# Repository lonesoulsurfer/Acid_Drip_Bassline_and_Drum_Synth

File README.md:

# Acid Drip - Bassline Synth, Drift Synth & Drum Machine

Youtube Video (click the image) -  

An RP2040-based acid bassline synthesizer and drum machine built on the Mozzi audio library. Three instruments in one device: a 16-step acid sequencer, a second synth voice called DRIFT, and a 16-pattern drum groove box, all running simultaneously on dual cores with a 320x240 ILI9341 TFT display and 16 Cherry MX pads.

NOTE: the images of the synth are V1. V2 is what I have provided in this repo and looks a little different (extra pot for mix added).

NOTE: V5 firmware adds a second synth voice called DRIFT, pattern chaining for the acid save slots, a MIX EDIT mode for balancing all three engines against each other, and a user editable custom drum pattern, on top of everything V4 had. See DRIFT Synth, Pattern Chaining, MIX EDIT and Custom Pattern below for each.

<p align="center">
  
  &nbsp;
  
  &nbsp;
  
</p>

---

## Hardware

| Component | Detail |
|-----------|--------|
| MCU | RP2040 (Raspberry Pi Pico or equivalent) |
| Display | ILI9341 320x240 TFT |
| Pads | 16x Cherry MX switches (2 rows of 8) |
| Pots | 3x analog (CUT, RES, DECAY) |
| Audio out (acid) | GP15 -> 100R + 10nF RC filter -> 3.5mm jack |
| Audio out (drums) | GP2 -> 470R resistor -> 3.5mm jack. In V5 this output also carries the DRIFT synth voice, summed with the drums |
| Sync in/out | GP2 (hardware SPDT switch selects drum/DRIFT audio OR sync). Direction (in or out) is chosen from an on-screen menu at boot, see Sync In/Out below |

### Wiring

```
TFT   : SCK=GP6  SDA=GP7  RST=GP8  DC=GP10  CS=GP13
Pots  : CUT=GP26  RES=GP28  DCY=GP27
Sync  : IN/OUT=GP2
Audio : Acid=GP15   Drums/DRIFT=GP2

Top row pads (steps 1-8):
  GP14=pad1  GP12=pad2  GP11=pad3  GP16=pad4
  GP17=pad5  GP19=pad6  GP20=pad7  GP21=pad8

Bottom row pads (steps 9-16 / FUNC select):
  GP0=pad9   GP1=pad10  GP3=pad11  GP4=pad12
  GP5=pad13  GP9=pad14  GP18=pad15 GP22=pad16
```

---

## Dependencies

Install via Arduino Library Manager:

- **Mozzi** (audio synthesis engine)
- **Adafruit GFX**
- **Adafruit ILI9341**

Board package: **Raspberry Pi Pico/RP2040** (Earle Philhower core)

---

## Files

This repo has two firmware versions, each in its own folder. They are separate sketches, not meant to be merged.

### V4 (`Acid_Drip_Drum_Acid_V4`)

| File | Description |
|------|-------------|
| `Acid_Drip_V4.ino` | Main sketch, acid synth engine, sequencer, UI |
| `BeatMachine_V4.ino` | Drum machine tab, DrumKid engine, 8 instruments |
| `beats.h` | 16 preset drum patterns (techno, house, hip-hop, etc.) |
| `sample0-7.h` | Drum samples stored as int8 arrays in flash (PROGMEM) |

### V5 (`Acid_Drip_Drum_Acid_Drift_V5`)

| File | Description |
|------|-------------|
| `Acid_Drip_V5_Drum_Acid_Drift.ino` | Main sketch, acid synth engine, sequencer, UI, MIX EDIT |
| `Drift.ino` | DRIFT tab, the second synth voice engine |
| `BeatMachine2.ino` | Drum machine tab, DrumKid engine, 8 instruments, custom pattern editor |
| `beats.h` | 16 drum patterns: 15 fixed presets plus one user editable CUSTOM slot |
| `sample0-7.h` | Drum samples stored as int8 arrays in flash (PROGMEM) |

V5 adds a second synth voice (DRIFT), pattern chaining, per engine level mixing (MIX EDIT), and a user editable custom drum pattern, all on top of everything V4 already had. Pick whichever folder matches the firmware you want to flash.

---

## Acid Synthesizer

### Pad Layout

```
+---------+---------+---------+---------+---------+---------+---------+---------+
|    1    |    2    |    3    |    4    |    5    |    6    |    7    |    8    |
|  step   |  step   |  step   |  step   |  step   |  step   |  step   |  step   |
|    1    |    2    |    3    |    4    |    5    |    6    |    7    |    8    |
+---------+---------+---------+---------+---------+---------+---------+---------+
|    9    |   10    |   11    |   12    |   13    |   14    |   15    |   16    |
|   KEY   |  RIFF   |  SOUND  |  WALK   |   FX    |  TEMPO  |  PLEN   |  PAT>   |
+---------+---------+---------+---------+---------+---------+---------+---------+
  (bottom row labels show only in FUNC mode)
```

### Step Editing

| Action | Result |
|--------|--------|
| Short press a pad | Toggle step on/off |
| Long press x1 | Toggle accent |
| Long press x2 | Toggle glide |
| Hold pad + turn CUT pot | Set step note (scale-quantised) |

### Chords

| Chord | Action |
|-------|--------|
| Pads 1+2 | Play / Stop |
| Pads 1+2 (hold 0.5s) | Factory reset. V5 scopes this to whichever engine is currently the edit focus: acid or DRIFT. Drums have their own separate reset, hold pads 1+2 for 1s while in drum mode |
| Pads 7+8 | Enter / exit FUNC mode |
| Pads 9+10 | Switch to drums (from acid or DRIFT), or back to whichever of acid/DRIFT was last active (from drums) |
| Pads 9+10+11 (hold 0.5s) | V5 only. From acid: go to DRIFT. From DRIFT: back to acid. From drums: no-op, see DRIFT Synth below |
| Pads 11+12+13+14 (hold 1s) | Toggle Acid Walks easter egg |
| Pads 12+13 | Enter / exit chain-build mode |
| Pads 15+16 (hold 1s) | V5 only. Toggle MIX EDIT mode (replaces V4's Accent Edit, see below) |

### Save / Load (hold pads 7+8)

- **Tap** pads 3/4/5/6 to load from slot 1/2/3/4
- **Hold** pads 3/4/5/6 for 1 second to save to slot 1/2/3/4
- Slot status shown top-right (yellow dot = saved, grey = empty)

In V5, each slot saves and loads the acid pattern, DRIFT, and the drum beat together, whichever of the three actually have data saved in that slot. The gesture is identical from the acid screen or the drum screen; either one saves and loads all three engines at once. Loading a slot also restores each engine's play/stop state exactly as it was at save time: an engine that was stopped when you saved goes silent on load even if it is currently playing, and an engine that was playing starts up again, in sync with the others. Any engine with no data in that slot is left exactly as it currently is. Tapping an empty slot shows an "empty" indicator instead of loading anything. In V4, a slot only covered whichever single engine you were on when you saved, and play state was not part of it.

Holding pads 3+4+5+6 together for 1 second, while on the acid or DRIFT screen, wipes the acid pattern out of all 4 slots at once (a "clear all" separate from the per-slot save/hold gesture above). Because V5 slots hold all three engines together, this only clears the acid portion of each slot; any DRIFT or drum data saved in those same slot numbers is left alone. This gesture is unchanged from V4, it was already in the firmware but missing from this document.

### Pattern Chaining (V5 only)

Link the 4 save slots into a longer playback sequence, up to 16 positions, in any order, with repeats.

**Building a chain:**

1. Tap pads 12+13 together to enter chain-build mode. The screen switches to a dedicated chain-builder view.
2. Tap pads 3/4/5/6 to append that slot to the chain. Tapping the same pad more than once repeats that slot, for example tapping 3, 3, 4, 5, 6, 6 builds a chain that plays slot 1 twice, then slot 2, slot 3, and slot 4 twice.
3. Tap pads 12+13 again to exit and start playback. The chain begins automatically, even if nothing was playing yet.

Each chain position plays through one full loop of that slot's own saved pattern length before advancing to the next position: a slot saved at 16 steps plays 16 steps, a slot saved at 8 steps plays 8, and so on. When the chain reaches the end it loops back to the first position.

Pads 7+8 (FUNC) cancel an in-progress build without starting playback. Tapping 12+13 again at any other time, including while a chain is already playing, drops the current chain and starts a fresh build.

A small "CH" indicator appears next to the slot status dots whenever a chain is actively playing.

Chains are session-only and are not saved to EEPROM, so rebuilding one takes a few seconds if needed again after a power cycle. Chaining currently works in the acid synth only, not drum mode.

### FUNC Mode (enter with pads 7+8)

| Pad | Function | Options |
|-----|----------|---------|
| 9 | KEY | Root note: C D Eb F G Ab Bb B |
| 10 | RIFF | Load preset riff pattern: DFLT / SQNCE / FUNK / MINI / JUMP / RAVE / SYNC / DARK |
| 11 | SOUND | Synth voice: SAW / SQR / SINE / PWM / CSAW / CSQR / CSIN / SUBSQ |
| 12 | WALK | Note walk: OFF / 4TH / OCTWAVE / 5TH / BOUNCE / MIN3RD / VAMP3 / RANDOM |
| 13 | FX | Enter FX assign sub-mode |
| 14 | TEMPO | Preset BPM: 100/110/120/128/133/138/145/160, or tap repeatedly for tap tempo |
| 15 | PLEN | Pattern length: 1 / 2 / 3 / 4 / 6 / 8 / 12 / 16 |
| 16 | PAT> | Playback order: FWD / CW / ALT / REV / SKIP2 / SKIP3 / PING / RND |

> Note: there is currently no live scale-type or octave selector. `seq.scale`/`seq.octave` are only set when loading a saved patch slot.

### FX Assign (FUNC -> pad 13)

1. Press a top-row pad to select an effect:
   `None / Oct Up / Retrigger / Stutter / Maj Step / Min Step / Dom7 Step / Dim Step`
2. Press any pad 1-16 to assign that effect to that step.
3. Tap the selected FX pad again to deselect.
4. Long-hold pad 1 to clear all step effects.
5. Pads 7+8 to exit back to main screen.

### MIX EDIT (V5 only)

Hold **pads 15+16** for 1 second to enter MIX EDIT. The three pots trim the output level of each of the three engines independently:

| Pot | Engine |
|-----|--------|
| CUT | Acid |
| RES | DRIFT |
| DCY | Drums |

This is a digital trim sitting on top of the physical mix pot, which only ever blends acid (GP15) against DRIFT plus drums (GP2) as one combined pair. MIX EDIT is what actually lets DRIFT be balanced against drums on its own, which the physical pot alone cannot do. Pot pickup applies here too: each pot stays inert until it has been moved past its position at the moment MIX EDIT was entered, so opening the page never snaps a level to wherever a pot happens to be sitting. Hold pads 15+16 again to exit; the three levels save to EEPROM automatically and persist across power cycles until changed again.

Accent Edit mode from V4 has been removed in V5 and replaced by MIX EDIT on the same pads 15+16 gesture. Accent tone is now a fixed setting rather than something you tune live.

### Acid Walks (Easter Egg)

Hold **pads 11+12+13+14** for 1 second to toggle a hidden mode with 8 preset patterns inspired by classic acid/house tracks, each pre-loaded with its own key, tempo, length and sound. Select a pattern with pads 1-8. FUNC mode, FX assignment and drum mode all continue to work normally while active. Hold the same 4-pad chord again to exit.

---

## DRIFT Synth (V5 only)

DRIFT is a second, independent synth voice that sits alongside the acid engine, with its own 16 step pattern, its own bank of 16 selectable synth engines, and its own FUNC page. It renders digitally and sums with the drum machine on the GP2 output, so DRIFT is only heard through the drums/DRIFT output, not the acid output.

### Switching to DRIFT

Which screen pads 9+10 and 9+10+11 land you on depends on where you currently are, not a fixed rule, so here is the full table:

| Currently on | Pads 9+10 | Pads 9+10+11 (hold 0.5s) |
|---------------|-----------|---------------------------|
| Acid | Go to drums | Go to DRIFT |
| DRIFT | Go to drums | Back to acid |
| Drums | Back to whichever of acid/DRIFT was active before | No-op, stays in drums |

DRIFT is only reachable from the acid screen, not directly from drums. Pressing 9+10+11 while already in drums is a deliberate no-op rather than a shortcut into DRIFT, since a three-pad press is easy to land imprecisely and jumping straight into DRIFT from drums made it too easy to end up somewhere unintended. To get from drums to DRIFT, go back to acid first (9+10), then 9+10+11.

Switching edit focus only changes which engine the pads and pots are currently controlling, not what is audible. Acid, DRIFT and drums can all be playing at once; each is started independently and the overall balance is set by the physical mix pot and MIX EDIT (see above).

### Step Editing

Once DRIFT is the edit focus, the same 16 pad grid used for acid steps toggles DRIFT's own step pattern instead. Holding a key on the KBRD page (see FOLW below) transposes the running line live while held.

### FUNC Mode (DRIFT)

With DRIFT as the edit focus, pads 7+8 open DRIFT's own FUNC page, separate from the acid FUNC page:

| Pad | Function | Options |
|-----|----------|---------|
| 9 | SND1 | Synth engine, page 1 of 2: SUBSIN / DTSQR / FMBEL / RINGM / CLICK / FOLDR / PWM / UNISN |
| 10 | SND2 | Synth engine, page 2 of 2: SAW / SUBDIV / NOIZ / VOWEL / ARPG / GONG / CRUSH / GATE |
| 11 | FOLW | Pitch mode: F+8 / F-8 / F+5 / F+3 (follow the acid voice's last note, plus an interval) / FOLW (plain follow) / ARP+ / AR+- / WALK |
| 12 | ECHO | Delay: OFF / 8D / 1/4 / 4D / 1/2 / 8FB / 4FB / 2FB |
| 13 | VERB | Reverb size: OFF / SML / MED / BIG / HALL / MEDW / BIGW / WASH |
| 14 | PATT | 8 user savable pattern slots, S1 to S8. See PATT below |
| 15 | EVOL | EVOLVE generative mutation: OFF / OCTL / ADD1 / DEEP / STUT / HVY / WILD / MAX |
| 16 | REC | Pot motion recorder. See REC below |

Each of the 16 synth engines maps the CUT/RES/DCY pots slightly differently (roughly octave, a character/detune/amount control, and decay time), so the same three pots do different things depending which engine is selected.

### PATT (pattern slots)

8 slots (S1 to S8) hold DRIFT's own saved step patterns, separate from the acid save slots. A tap loads a slot (blank if nothing has been saved there yet); a hold saves whatever is currently on the grid as that slot. All 8 slots start blank. These are on/off step patterns only; what note actually plays at each step is decided separately by the FOLW/pitch mode.

### EVOLVE (EVOL)

A generative mutation system with 7 named intensity modes (OCTL / ADD1 / DEEP / STUT / HVY / WILD / MAX) on top of OFF. When active, EVOLVE periodically nudges the DRIFT line away from its recorded pattern and back again; the mode selected sets how far it wanders and how often.

### Pot Motion Recorder (REC)

Short-tap the REC pad (16) to start recording, tap again to stop. While recording, moving any of the three pots arms that pot's lane and captures its position on every step for one loop of the pattern. Release REC and the recorded lanes play back automatically each step, in time, while any pot you did not record stays live and playable as normal. Long-press REC to clear all recorded lanes. This lets a single loop carry pot automation, for example a filter sweep or a pitch rise that repeats every bar, without needing to hold the pot yourself.

---

## Beat Machine

Switch between acid and drum mode by pressing **pads 9+10 simultaneously**. In V5, holding pads 9+10+11 instead switches to DRIFT (see DRIFT Synth above). The sequencer state is preserved when switching between any of the three.

### Drum Instruments (8 tracks)

| Pad | Instrument |
|-----|-----------|
| 1 | Kick |
| 2 | Hi-hat (closed) |
| 3 | Snare |
| 4 | Rim |
| 5 | Tom |
| 6 | Bass 2 |
| 7 | Clap |
| 8 | Open hat |

### Pattern Selection

Short-tap any pad (1-16) to load that beat pattern. The current pattern name and number are shown on the display. Pads 1-5 double as drum edit pads (see below): a short tap selects the pattern, a long hold enters drum editing. In V5, pad 16 has an additional role: it also opens the CUSTOM pattern editor (see Custom Pattern below).

### Per-Drum Editing

Hold any of pads 1-5 (kick/hat/snare/rim/tom) and turn the pots:

- **CUT** -> pitch (exponential, pot centre = natural speed, each 64 units = one octave)
- **RES** -> decay length (exponential envelope from a 4ms blip to full sample tail)
- **DCY** -> volume

Pot pickup prevents value jumps when grabbing a control: each pot only responds once it has been physically moved past its position at the moment the pad was grabbed. Per-drum settings reset on pattern change and are saved with slots.

> Bass 2, Clap, and Open Hat (pads 6-8) cannot be edited via hold+pot. Pattern selection is their only pad function.

### Beat Machine FUNC Mode (pads 7+8)

| Label | Function | Detail |
|-------|----------|--------|
| PTCH | Global pitch | Transposes all drums together; stacks on top of per-drum pitch |
| DRIV | Drive / saturation | Exponential pre-gain into a hard-knee saturator; top of the knob also adds bit crush |
| FILT | Bipolar DJ filter | Centre = bypass; below centre = lowpass sweep; above centre = highpass sweep |
| CHNC | Chance | Centre = as-is; below = thins existing hits (anchors held solid); above = adds ghost hits on empty steps |
| HMNZ | Humanize | Adds random velocity spread and per-hit micro-timing jitter; centre = robotic |
| SWNG | Swing | Delays odd 16th steps up to 60% of the step interval for a swung feel |
| ACNT | Accent depth | Centre = flat; above centre = on-beat emphasis; below centre = off-beat (pushed) emphasis |
| FILL | Procedural fill engine | See Fill Engine below |

All FUNC parameters except FILT and CHNC are saved with slots.

### Fill Engine (FUNC -> FILL)

The fill engine takes over the last few steps before a pattern boundary with a procedurally generated build, then lands on beat 1 with a kick and open hat.

**Pads 1-4** set the fill frequency:

| Pad | Label | Behaviour |
|-----|-------|-----------|
| 1 | OFF | No fills |
| 2 | 1 BAR | Fill every 16 steps (4 steps long) |
| 3 | 2 BAR | Fill every 32 steps (6 steps long) |
| 4 | 4 BAR | Fill every 64 steps (8 steps long, half a bar) |

**Pads 5-8** set the fill type:

| Pad | Label | Behaviour |
|-----|-------|-----------|
| 5 | HATS | Closed-hat build opening to an open hat on the tail; kick holds the floor |
| 6 | CLAP | Clap build over a steady half-time kick |
| 7 | SNARE | Flat snare rush with no kick; the landing slams |
| 8 | KIT | Descending tom for the first 70% of the window, then snare into the landing; KIT also adds a clap on the "1" |

> Pads 7 and 8 are also the FUNC-exit chord. SNARE and KIT selections register on release so the exit gesture takes priority.

**Editing the fill sound:** while in the FILL slot, the three pots control the lead voice's own pitch, decay length, and volume independently of the pattern's drum settings. These are saved with slots.

Density accelerates into the landing: the final quarter of the fill window schedules additional 32nd-note in-between hits so the build feels like it rushes into the "1".

### Preset Patterns

16 patterns selectable from the pad grid:

| # | Short name | Full name |
|---|-----------|-----------|
| 1 | BASC | BASIC |
| 2 | HOUS | HOUSE |
| 3 | TECH | TECHNO |
| 4 | ACID | ACID TRACK |
| 5 | HSOC | HI STATE |
| 6 | FUNK | FUNKY |
| 7 | SWNG | SWING |
| 8 | BKBT | BREAKBEAT |
| 9 | MINM | MINIMAL |
| 10 | LATN | LATIN |
| 11 | PCFC | PACIFIC ST |
| 12 | BLMN | BLUE MONDAY |
| 13 | DNBT | DRUM N BASS |
| 14 | VOOD | VOODOO RAY |
| 15 | GBLD | BUILD DOWN |
| 16 | CUST | CUSTOM (V5 only, user editable, see Custom Pattern below) |

> V4's pattern 16 was a fixed preset called JACK BEAT. V5 replaces it with the user editable CUSTOM slot described below.

### Custom Pattern (Pad 16, V5 only)

Pattern slot 16 is CUSTOM: a blank, user editable pattern rather than a fixed preset.

- **Quick tap pad 16** while not already editing to enter custom edit mode straight away. No hold required.
- **Tap pad 16** again once you are editing to toggle step 16 for whichever drum voice is currently selected, the same as tapping any other step pad.
- **Turn any pot** at any time while editing to set pitch/length/volume for the current voice, live, the same as normal per-drum editing.
- **Hold pad 16 for 0.4 seconds** to cycle to the next drum voice.
- **Hold pad 16 for 0.8 seconds** to exit and save.
- **Hold pad 16 for 2 seconds**, from either state, to wipe the whole custom pattern and start again.

A live legend appears along the bottom of the screen the moment pad 16 is pressed, listing each of the tiers above. They start out white and light up in their own colour as your hold time reaches that tier, so you can see what letting go will do before you commit to it.

### Save / Load (drum mode)

Same gesture as the acid synth: hold pads 7+8, then tap pads 3-6 to load from slot 1-4 or hold pads 3-6 for one second to save. This is the same unified save/load described above, it saves and loads acid, DRIFT and the drum beat together (including each engine's play/stop state) no matter which screen you trigger it from. Per-drum pitch/length/volume, global FUNC parameters, tempo, swing, fill settings, and the selected pattern are all stored as part of it.

Holding pads 3+4+5+6 together for 1 second while in drum mode (and not holding pads 7+8) wipes the drum beat out of all 4 slots at once, the drum-side equivalent of the acid clear-all gesture above. It only clears the drum portion of each slot; acid and DRIFT data saved in those same slot numbers is untouched.

---

## Sync In / Sync Out / Drum Mode (GP2)

GP2 is shared between drum audio output (in V5, also the DRIFT synth voice, which sums with the drums on the same output) and the sync clock jack, in either direction. A physical **SPDT switch on the PCB** routes the pin to either function.

**Boot detection selects the mode and, for sync, the direction:**

- **Drum mode (default):** GP2 is claimed by PWMAudio DMA and outputs drum (and, in V5, DRIFT) audio. Switch in the DRUMS position. Hold nothing at power-on.
- **Sync In mode:** Hold **pad 14** at power-on. A "SYNC MODE" menu appears; press **pad 1** for Sync In. GP2 is configured as a digital input and listens for an external clock pulse, driving this device's tempo from it. Switch in the SYNC position.
- **Sync Out mode:** Hold **pad 14** at power-on. On the same "SYNC MODE" menu, press **pad 2** for Sync Out. GP2 becomes a clock output instead, generating a DIN-sync-style pulse train (24 pulses per quarter note, matching the TB-303/808/909 standard) from this device's own tempo, so it can drive other gear as the master. Switch in the SYNC position.

A cyan "SYNC MODE" menu appears when pad 14 is held at boot, prompting for pad 1 (Sync In) or pad 2 (Sync Out); a "SYNC IN ACTIVE" or "SYNC OUT ACTIVE" confirmation follows briefly once chosen.

Sync Out only emits pulses while the acid transport is running (pads 1+2). It goes idle (line held low) when stopped rather than free-running through a stopped pattern. The pulse width is fixed at 2ms regardless of tempo. The info bar's "S" indicator (top right) is cyan for Sync In and magenta for Sync Out, so you can tell direction at a glance while playing.

> The switch position and the held pad must match. If the switch is in SYNC position but the device boots into drum mode, GP2 will try to drive audio into the sync signal line. In V5, sync mode (either direction) silences drums and DRIFT together, since both share GP2 with the sync jack; the acid voice on GP15 is unaffected either way. Sync In and Sync Out cannot run at the same time, since they both need sole use of GP2, one as an input, one as an output; the boot menu is where you pick one for that session.

---

## Architecture Notes

The firmware runs on both RP2040 cores:

- **Core 0**: Mozzi audio engine (acid synthesis, DRIFT synthesis in V5, and drum mixing), pad scanning, sequencer logic
- **Core 1**: TFT display rendering, drum sample buffer filling (via `bmFillDrumBuffer`)

The two cores communicate via the RP2040 inter-core FIFO. All SPI/TFT calls happen exclusively on core 1.

The drum clock is driven directly by the acid sequencer's `advanceStep()` call rather than an independent timer. In V5, DRIFT's own step advance is driven from the same call. This guarantees zero drift between all engines at all tempos and pattern lengths.

The drum audio path on GP2 uses a separate `PWMAudio` DMA instance at 488kHz carrier (versus Mozzi's 48kHz on GP15). This prevents carrier-frequency beating between the two audio outputs that would otherwise cause the acid synth to sound quieter when drums (and, in V5, DRIFT) are playing. DRIFT is rendered digitally and summed into this same GP2 path alongside the drums, rather than having a separate output of its own.

MIX EDIT's per-engine levels (V5) are a digital trim applied on top of this, independent of the physical mix pot, and are stored in EEPROM alongside the other saved settings.

---

## Credits

- Acid synthesis engine adapted from *Badass Bass*  https://www.youtube.com/watch?v=MvDILHYImc4
- Drum engine adapted from **DrumKid** by Matt Bradshaw  https://www.youtube.com/watch?v=509iZGjnVhM
- Built with the [Mozzi](https://sensorium.github.io/Mozzi/) audio library
- Hardware design and firmware by Marcus ([lonesoulsurfer](https://github.com/lonesoulsurfer))

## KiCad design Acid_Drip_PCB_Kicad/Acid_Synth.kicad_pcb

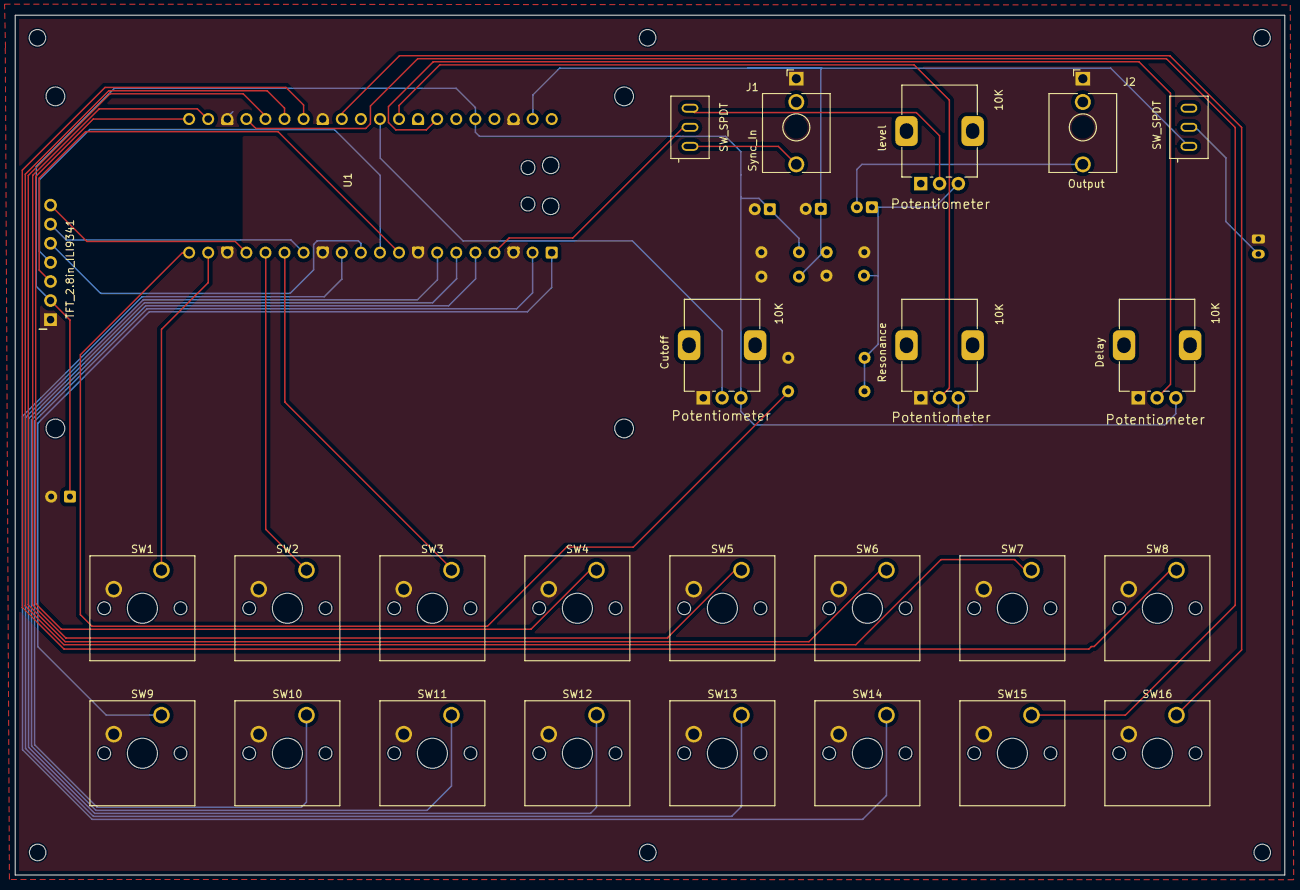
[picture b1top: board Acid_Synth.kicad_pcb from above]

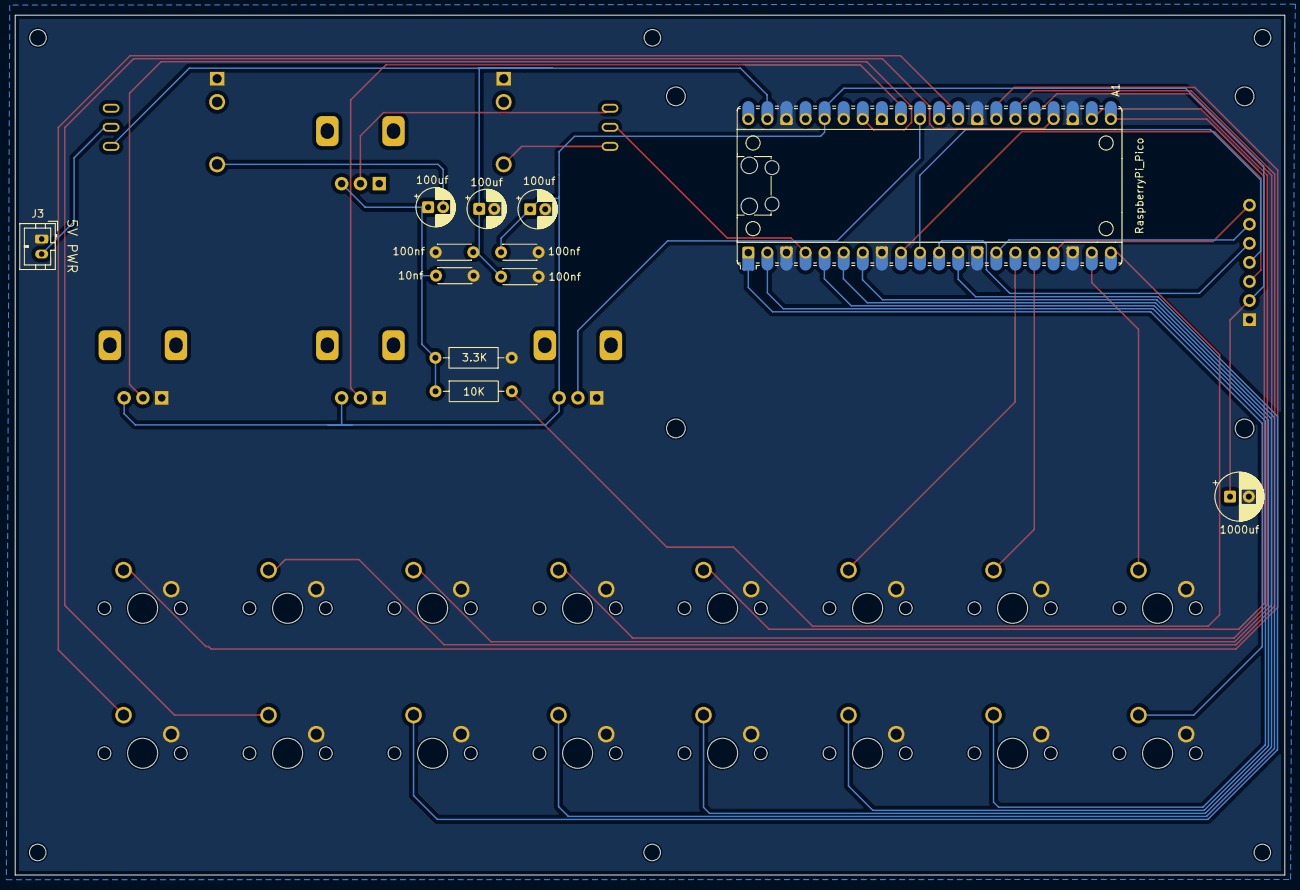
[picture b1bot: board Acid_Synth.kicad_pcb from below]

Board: 2 copper layers, 169.0 x 114.4 mm, 37 parts (12 on the bottom side), 33 nets.

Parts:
A1: RaspberryPi_Pico; RaspberryPi_Pico_Common
C1, C2, C4: 100nf; C_Disc_D4.3mm_W1.9mm_P5.00mm
C3, C5, C6: 100uf; CP_Radial_D5.0mm_P2.00mm
C7: 10nf; C_Disc_D4.3mm_W1.9mm_P5.00mm
C9: 1000uf; CP_Radial_D6.3mm_P2.50mm
Cutoff: 10K; Potentiometer_Alps_RK09K_Single_Vertical
Delay: 10K; Potentiometer_Alps_RK09K_Single_Vertical
J1: Sync_In; Jack_3.5mm_QingPu_WQP-PJ398SM_Vertical_CircularHoles
J2: Output; Jack_3.5mm_QingPu_WQP-PJ398SM_Vertical_CircularHoles
J3: Conn_01x02_Socket; JST_PH_B2B-PH-K_1x02_P2.00mm_Vertical
R1: 3.3K; R_Axial_DIN0207_L6.3mm_D2.5mm_P10.16mm_Horizontal
R3: 10K; R_Axial_DIN0207_L6.3mm_D2.5mm_P10.16mm_Horizontal
Resonance: 10K; Potentiometer_Alps_RK09K_Single_Vertical
SW1, SW2, SW3, SW4, SW5, SW6, SW7, SW8, SW9, SW10, SW11, SW12, SW13, SW14, SW15, SW16: SW_Cherry_MX_1.00u_PCB
SW17, SW18: SW_SPDT; SW_SPDT_Toggle_QuarterInch_Bushing
U1: TFT_2.8in_ILI9341
level: 10K; Potentiometer_Alps_RK09K_Single_Vertical

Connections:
+3.3V: A1.36 (3V3), C2.1, C3.1, C9.1, Cutoff.3, Delay.3, Resonance.3, U1.2 (VCC)
+5V: A1.39 (VSYS), C1.1, C4.1, C5.1, SW17.1 (A)
+BATT: J3.2, SW17.2 (B)
CS: A1.17 (GPIO13), U1.7 (CS)
Cutoff: A1.31 (GPIO26_ADC0), Cutoff.2
DC: A1.14 (GPIO10), U1.6 (DC)
Decay: A1.34 (GPIO28_ADC2), Delay.2
GND: A1.3 (GND), A1.8 (GND), A1.13 (GND), A1.18 (GND), A1.23 (GND), A1.28 (GND), A1.38 (GND), C1.2, C2.2, C3.2, C4.2, C5.2, C7.1, C9.2, Cutoff.1, Delay.1, J1.S, J2.S, J3.1, R1.1, Resonance.1, SW1.2, SW2.2, SW3.2, SW4.2, SW5.2, SW6.2, SW7.2, SW8.2, SW9.2, SW10.2, SW11.2, SW12.2, SW13.2, SW14.2, SW15.2, SW16.2, U1.1 (GND)
NODE: C6.1, C7.2, R1.2, R3.1, level.3
unnamed: C6.2, J2.T
unnamed: J1.T, SW18.1 (A)
OUTPUT: A1.20 (GPIO15), R3.2
RST: A1.11 (GPIO8), U1.5 (RST)
Resonance: A1.32 (GPIO27_ADC1), Resonance.2
SCL: A1.9 (GPIO6), U1.3 (SCL)
SDA: A1.10 (GPIO7), U1.4 (SDA)
SW1: A1.19 (GPIO14), SW1.1
SW2: A1.16 (GPIO12), SW2.1
SW3: A1.15 (GPIO11), SW3.1
SW4: A1.21 (GPIO16), SW4.1
SW5: A1.22 (GPIO17), SW5.1
SW6: A1.25 (GPIO19), SW6.1
SW7: A1.26 (GPIO20), SW7.1
SW8: A1.27 (GPIO21), SW8.1
SW9: A1.1 (GPIO0), SW9.1
SW10: A1.2 (GPIO1), SW10.1
SW11: A1.5 (GPIO3), SW11.1
SW12: A1.6 (GPIO4), SW12.1
SW13: A1.7 (GPIO5), SW13.1
SW14: A1.12 (GPIO9), SW14.1
SW15: A1.24 (GPIO18), SW15.1
SYNC_IN: A1.4 (GPIO2), SW18.2 (B)
W16: A1.29 (GPIO22), SW16.1

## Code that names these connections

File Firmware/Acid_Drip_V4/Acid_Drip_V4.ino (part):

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bool     accentEditMode  = false;  // true while CUT/RES/DECAY pots tune the accent envelope
bool     accentEditArmed = false;  // chord held, waiting for ACCENT_HOLD_MS
uint32_t accentEditArmMs = 0;
int16_t  accentEnvCutoff = 90;   // accent peak cutoff boost (0-255) — replaces hardcoded 90
int16_t  accentEnvRes    = 90;   // accent peak resonance boost (0-400) — replaces hardcoded 90
int16_t  accentDecayDiv  = 5;    // accent envelope decay divisor (1-10) — replaces hardcoded 5



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#define POT_CUT   26
#define POT_RES   28
#define POT_DECAY 27
#define SYNC_IN    2

// 16 pads — top row (steps 1-8): applies FUNC values / FX assign phase 1+2
//           bottom row (steps 9-16): selects FUNC function in FUNC mode
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volatile int16_t  gResonanceDisplay = 512;  // 0-1023 for bar display (512 = mid)
volatile int16_t  gVolSub    = 500;
volatile int16_t  gEnvCutoff = 0;    // envelope filter boost — peaks on note-on, decays with DCY
volatile int16_t  gEnvRes    = 0;    // accent resonance envelope boost — peaks on accented note-on, decays with DCY
volatile bool     gAccentActive = false;  // true while the current note's accent envelope is decaying
volatile uint8_t  gSound     = 0;
volatile uint8_t  gEffect    = 0;
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  }

  // Resonance smoothing — apply power curve to positive gResonance only.
  // The damping region (gResonance < 0) stays linear; the resonance peak region
  // builds gradually from zero instead of jumping abruptly at the pot midpoint.
  if (gResonance > 0 && gResonance < 512) {
    gResonance = (int16_t)resCurve[gResonance];
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
  if (syncMode) {
    // Sync mode: configure GP2 as digital input for sync clock
    pinMode(SYNC_IN, INPUT);
    // Do NOT call bmStartAudio() — GP2 stays as input
  }
  // Drum mode: GP2 claimed by PWMAudio DMA handles GPIO setup in bmStartAudio()
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
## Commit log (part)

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2026-06-11 Enhance credits section with video links
    Added video links for Acid synthesis engine and Drum engine credits.
2026-06-11 Revise README description for groove box clarity
    Updated description for clarity and consistency.
2026-06-11 Update number of analog pots from 3 to 4
2026-06-11 Fix formatting in README.md for clarity
